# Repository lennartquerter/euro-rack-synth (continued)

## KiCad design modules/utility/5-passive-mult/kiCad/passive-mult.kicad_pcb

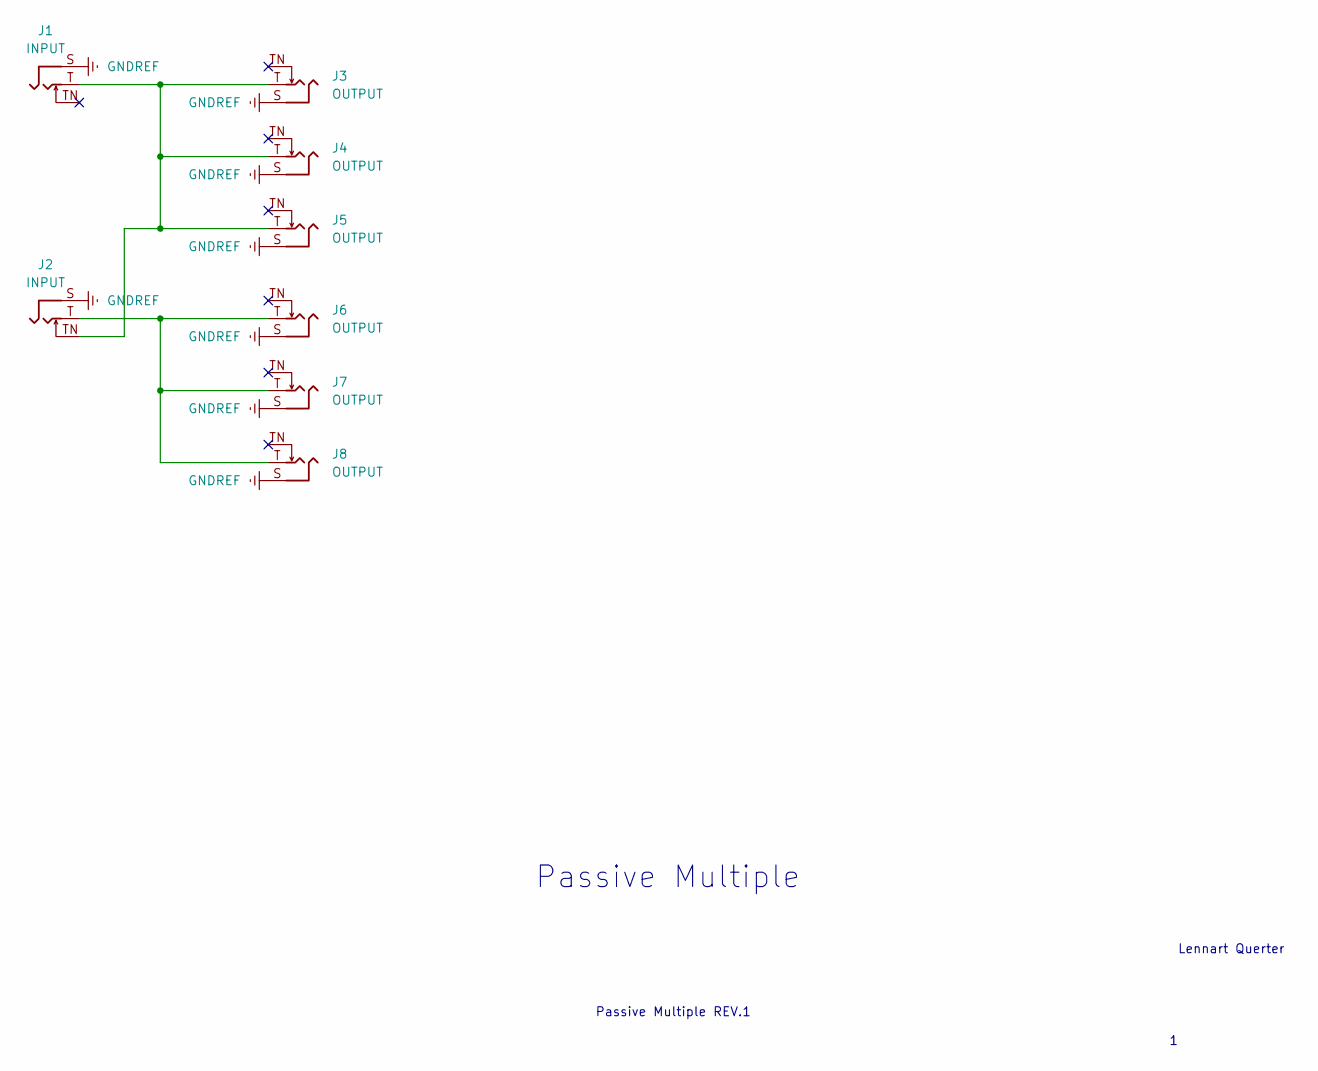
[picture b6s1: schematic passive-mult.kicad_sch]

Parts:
J1, J2: INPUT; Jack_3.5mm_QingPu_WQP-PJ398SM_tight-fit
J3, J4, J5, J6, J7, J8: OUTPUT; Jack_3.5mm_QingPu_WQP-PJ398SM_tight-fit

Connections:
GNDREF: J1.S, J2.S, J3.S, J4.S, J5.S, J6.S, J7.S, J8.S
unnamed: J1.T, J2.TN, J3.T, J4.T, J5.T
unnamed: J2.T, J6.T, J7.T, J8.T

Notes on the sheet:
Passive Multiple REV.1
Passive Multiple
Lennart Querter

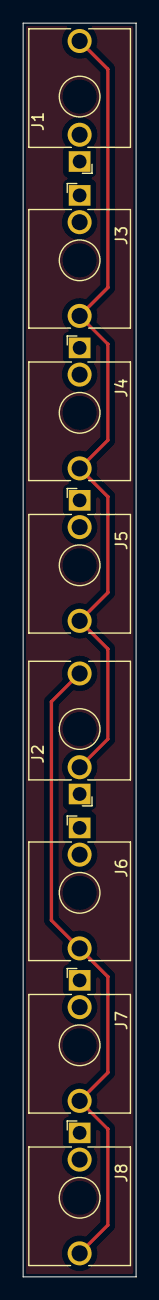
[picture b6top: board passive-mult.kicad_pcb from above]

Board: 2 copper layers, 10.0 x 111.0 mm, 8 parts (0 on the bottom side), 3 nets.
